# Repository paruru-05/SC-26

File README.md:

# パーツリストはPCB_Partsのそれぞれのファイルから読み取ってください。過去のものは不安定なため確定後に書き直します。

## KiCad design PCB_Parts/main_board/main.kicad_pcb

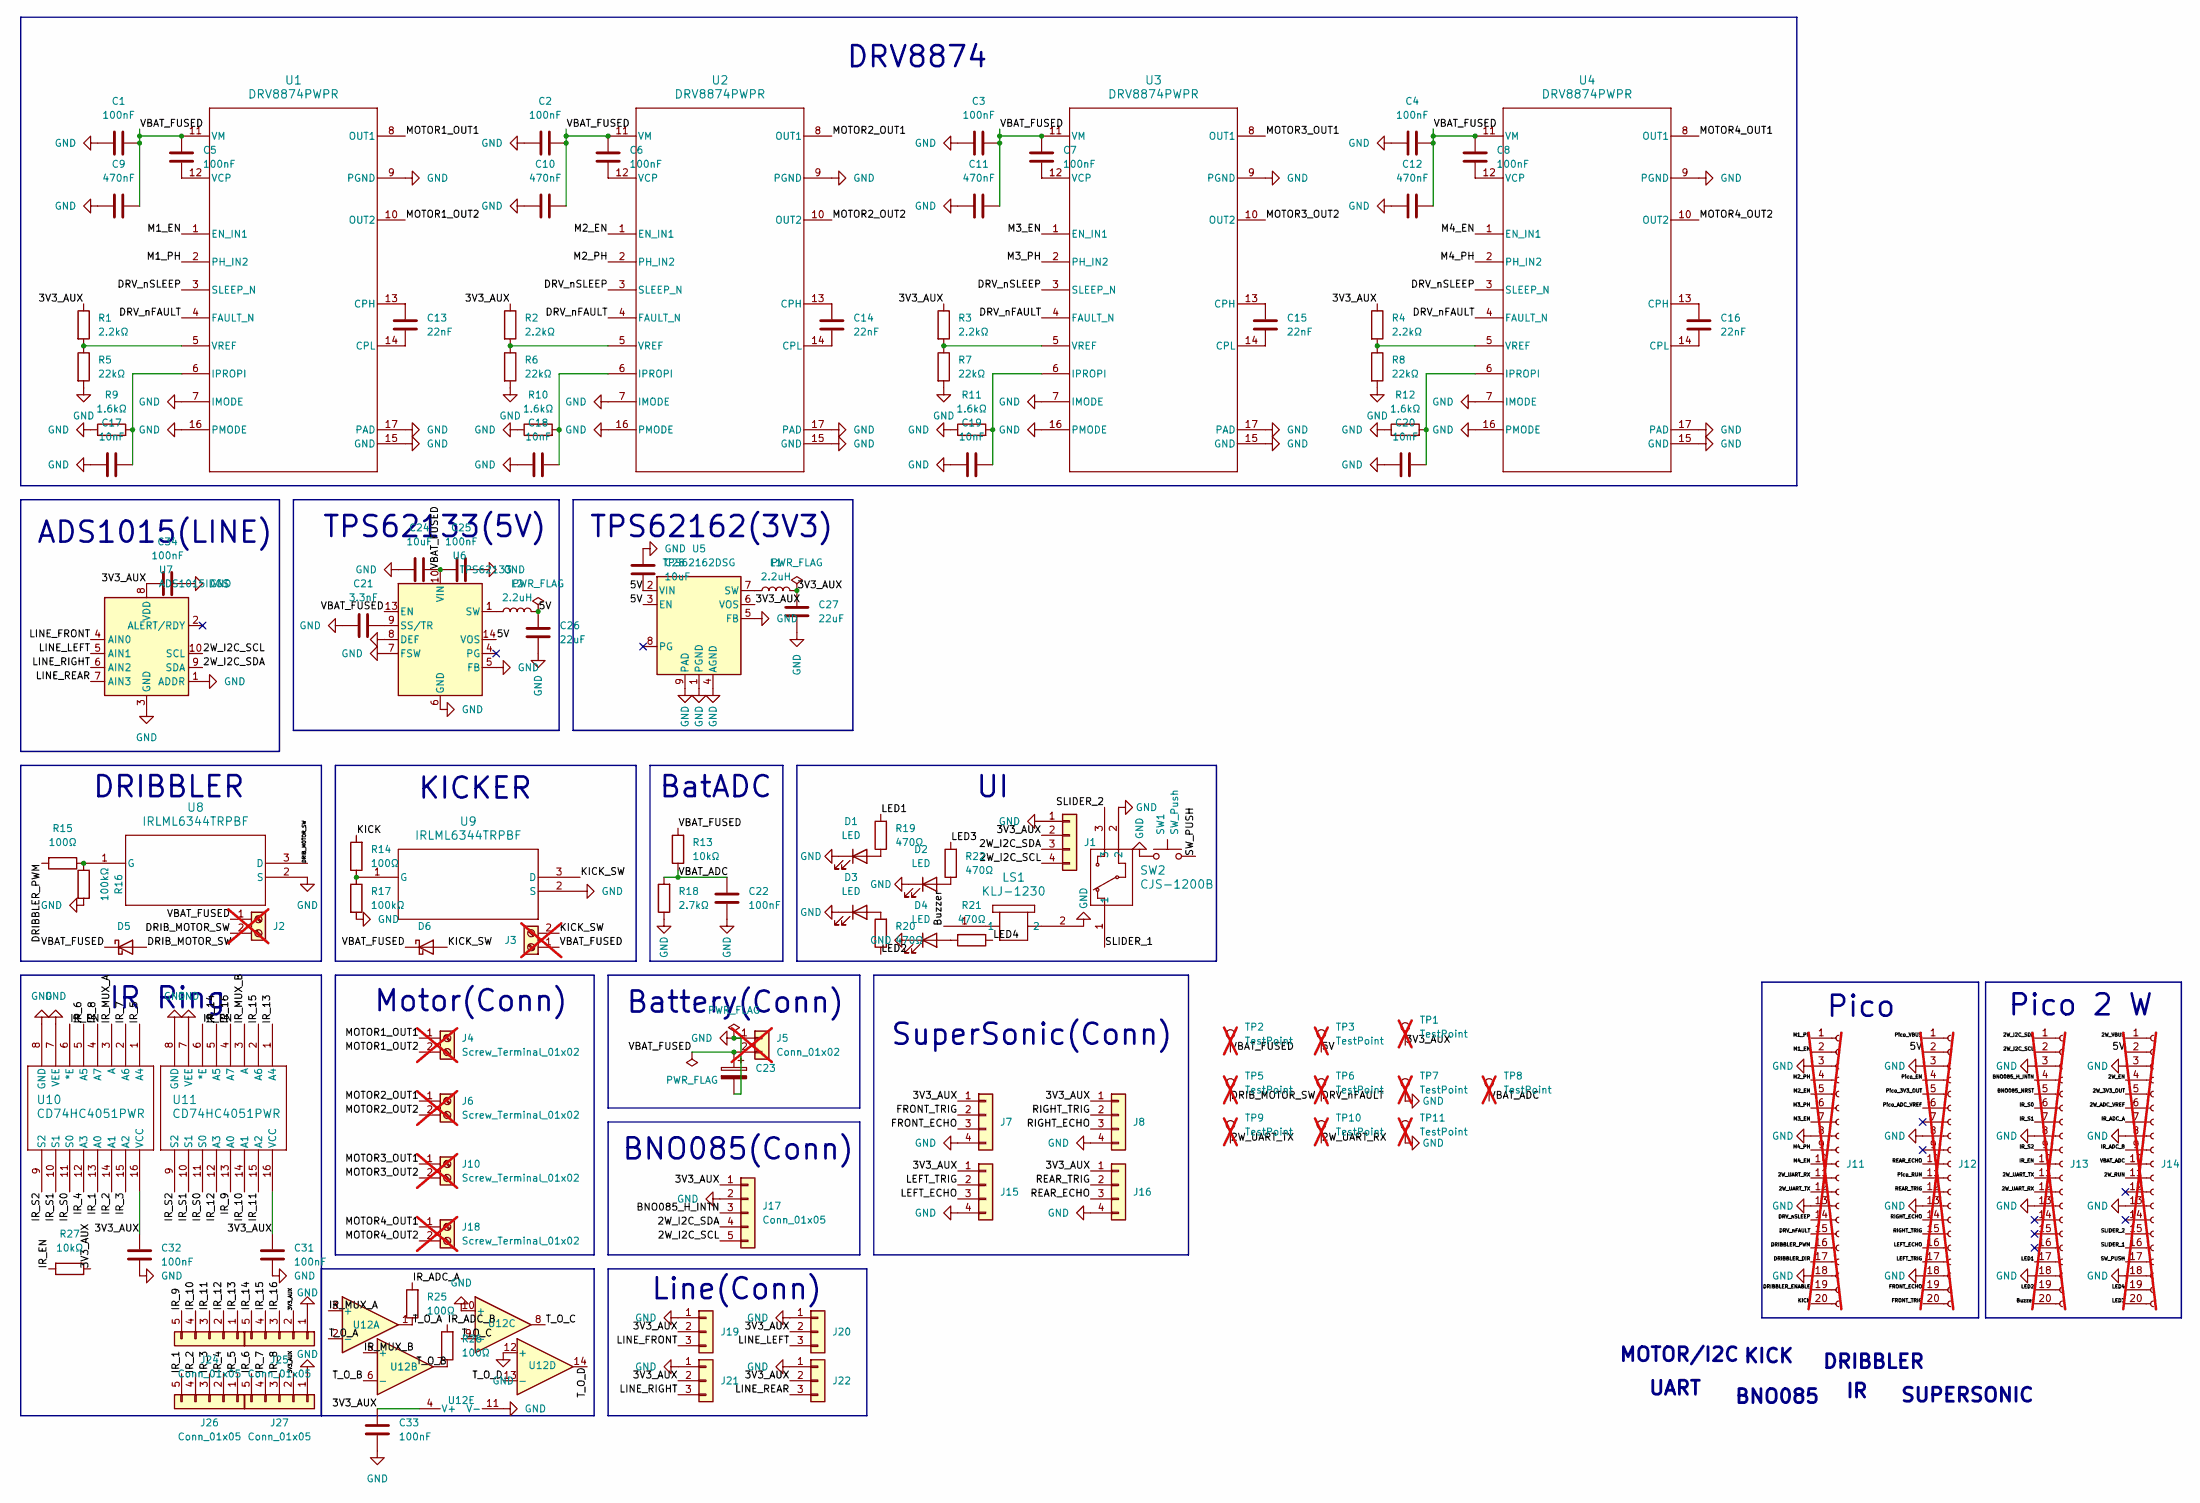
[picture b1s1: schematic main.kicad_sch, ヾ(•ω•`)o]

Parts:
C1, C2, C3, C4, C5, C6, C7, C8, C22, C25, C31, C32, C33, C34: 100nF; C_0603_1608Metric
C9, C10, C11, C12: 470nF; C_0603_1608Metric
C13, C14, C15, C16: 22nF; C_0603_1608Metric
C17, C18, C19, C20: 10nF; C_0603_1608Metric
C21: 3.3nF; C_0603_1608Metric
C23: 1000uF; CP_Elec_10x10.5
C24, C28: 10uF; C_1206_3216Metric
C26, C27: 22uF; C_1206_3216Metric
D1, D2, D3, D4: LED; LED_0603_1608Metric
D5, D6: D_Schottky; D_SMC
J1, J7, J8, J15, J16: Conn_01x04; CONN-SMD_B4B-PH-SM4-TB-LF-SN
J2, J3, J4, J6, J10, J18: Screw_Terminal_01x02; TerminalBlock_Phoenix_MKDS-1,5-2-5.08_1x02_P5.08mm_Horizont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; not fitted
J5: Conn_01x02; AMASS_XT30PW-M_1x02_P2.50mm_Horizontal; not fitted
J11, J12, J13, J14: Conn_01x20_Socket; PinSocket_1x20_P2.54mm_Vertical; not fitted
J17, J24, J25, J26, J27: Conn_01x05; CONN-SMD_5P-P2.00_B6B-PH-SM4-TB-LF-SN
J19, J20, J21, J22: Conn_01x03; CONN-SMD_B3B-PH-SM4-TB-LF-SN
L1, L2: 2.2uH; L_Coilcraft_XxL4020
LS1: KLJ-1230; KLJ-1230_KKG
R1, R2, R3, R4: 2.2kΩ; R_0603_1608Metric
R5, R6, R7, R8: 22kΩ; R_0603_1608Metric
R9, R10, R11, R12: 1.6kΩ; R_0603_1608Metric
R13, R27: 10kΩ; R_0603_1608Metric
R14, R15, R25, R26: 100Ω; R_0603_1608Metric
R16, R17: 100kΩ; R_0603_1608Metric
R18: 2.7kΩ; R_0603_1608Metric
R19, R20, R21, R22: 470Ω; R_0603_1608Metric
SW1: SW_Push; SW-SMD_L3.9-W3.0-P4.45
SW2: CJS-1200B; CJS-1200B_NDC
TP1, TP2, TP3, TP5, TP6, TP7, TP8, TP9, TP10, TP11: TestPoint; TestPoint_Pad_D3.0mm; not fitted
U1, U2, U3, U4: DRV8874PWPR; PWP0016J_N
U5: TPS62162DSG; Texas_DSG0008A_WSON-8-1EP_2x2mm_P0.5mm_EP0.9x1.6mm_ThermalV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
U6: TPS62133; VQFN-16-1EP_3x3mm_P0.5mm_EP1.68x1.68mm_ThermalVias
U7: ADS1015IDGS; TSSOP-10_3x3mm_P0.5mm
U8, U9: IRLML6344TRPBF; IRLML6344TRPBF_INF
U10, U11: CD74HC4051PWR; PW16
U12: TLV9064; TSSOP-14_4.4x5mm_P0.65mm

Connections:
/2W_3V3_OUT: J14.5
/2W_ADC_VREF: J14.6
/2W_EN: J14.4
/2W_I2C_SCL: J1.4, J13.2, J17.5, U7.10 (SCL)
/2W_I2C_SDA: J1.3, J13.1, J17.4, U7.9 (SDA)
/2W_RUN: J14.11
/2W_UART_RX: J11.11, J13.12, TP10.1 (1_1)
/2W_UART_TX: J11.12, J13.11, TP9.1 (1_1)
/2W_VBUS: J14.1
/3V3_AUX: C27.2, C31.1, C32.2, C33.1, C34.1, J1.2, J7.1, J8.1, J15.1, J16.1, J17.1, J19.2, J20.2, J21.2, J22.2, J25.2, J27.2, L1.2, R1.1, R2.1, R3.1, R4.1, R27.1, TP1.1 (1_1), U5.6 (VOS), U7.8 (VDD), U10.16 (VCC), U11.16 (VCC), U12.4 (V+)
/5V: C26.2, C28.2, J12.2, J14.2, L2.2, TP3.1 (1_1), U5.2 (VIN), U5.3 (EN), U6.14 (VOS)
/BNO085_H_INTN: J13.4, J17.3
/BNO085_NRST: J13.5
/Buzzer: J13.20, LS1.1
/DRIBBLER_DIR: J11.17
/DRIBBLER_ENABLE: J11.19
/DRIBBLER_PWM: J11.16, R15.2
/DRIB_MOTOR_SW: D5.2 (A), J2.2, TP5.1 (1_1), U8.3 (D)
/DRV_nFAULT: J11.15, TP6.1 (1_1), U1.4 (FAULT_N), U2.4 (FAULT_N), U3.4 (FAULT_N), U4.4 (FAULT_N)
/DRV_nSLEEP: J11.14, U1.3 (SLEEP_N), U2.3 (SLEEP_N), U3.3 (SLEEP_N), U4.3 (SLEEP_N)
/FRONT_ECHO: J7.3, J12.19
/FRONT_TRIG: J7.2, J12.20
/IR_1: J26.5, U10.13 (A0)
/IR_2: J26.4, U10.14 (A1)
/IR_3: J26.3, U10.15 (A2)
/IR_4: J26.2, U10.12 (A3)
/IR_5: J26.1, U10.1 (A4)
/IR_6: J27.5, U10.5 (A5)
/IR_7: J27.4, U10.2 (A6)
/IR_8: J27.3, U10.4 (A7)
/IR_9: J24.5, U11.13 (A0)
/IR_10: J24.4, U11.14 (A1)
/IR_11: J24.3, U11.15 (A2)
/IR_12: J24.2, U11.12 (A3)
/IR_13: J24.1, U11.1 (A4)
/IR_14: J25.5, U11.5 (A5)
/IR_15: J25.4, U11.2 (A6)
/IR_16: J25.3, U11.4 (A7)
/IR_ADC_A: J14.7, R25.2
/IR_ADC_B: J14.9, R26.2
/IR_EN: J13.10, R27.2, U10.6 (*E), U11.6 (*E)
/IR_MUX_A: U10.3 (A), U12.3 (+)
/IR_MUX_B: U11.3 (A), U12.5 (+)
/IR_S0: J13.6, U10.11 (S0), U11.11 (S0)
/IR_S1: J13.7, U10.10 (S1), U11.10 (S1)
/IR_S2: J13.9, U10.9 (S2), U11.9 (S2)
/KICK: J11.20, R14.2
/KICK_SW: D6.2 (A), J3.2, U9.3 (D)
/LED1: J13.17, R19.2
/LED2: J13.19, R20.1
/LED3: J14.20, R22.2
/LED4: J14.19, R21.1
/LEFT_ECHO: J12.16, J15.3
/LEFT_TRIG: J12.17, J15.2
/LINE_FRONT: J19.3, U7.4 (AIN0)
/LINE_LEFT: J20.3, U7.5 (AIN1)
/LINE_REAR: J22.3, U7.7 (AIN3)
/LINE_RIGHT: J21.3, U7.6 (AIN2)
/M1_EN: J11.2, U1.1 (EN_IN1)
/M1_PH: J11.1, U1.2 (PH_IN2)
/M2_EN: J11.5, U2.1 (EN_IN1)
/M2_PH: J11.4, U2.2 (PH_IN2)
/M3_EN: J11.7, U3.1 (EN_IN1)
/M3_PH: J11.6, U3.2 (PH_IN2)
/M4_EN: J11.10, U4.1 (EN_IN1)
/M4_PH: J11.9, U4.2 (PH_IN2)
/MOTOR1_OUT1: J4.1, U1.8 (OUT1)
/MOTOR1_OUT2: J4.2, U1.10 (OUT2)
/MOTOR2_OUT1: J6.1, U2.8 (OUT1)
/MOTOR2_OUT2: J6.2, U2.10 (OUT2)
/MOTOR3_OUT1: J10.1, U3.8 (OUT1)
/MOTOR3_OUT2: J10.2, U3.10 (OUT2)
/MOTOR4_OUT1: J18.1, U4.8 (OUT1)
/MOTOR4_OUT2: J18.2, U4.10 (OUT2)
/Pico_3V3_OUT: J12.5
/Pico_ADC_VREF: J12.6
/Pico_EN: J12.4
/Pico_RUN: J12.11
/Pico_VBUS: J12.1
/REAR_ECHO: J12.10, J16.3
/REAR_TRIG: J12.12, J16.2
/RIGHT_ECHO: J8.3, J12.14
/RIGHT_TRIG: J8.2, J12.15
/SLIDER_1: J14.16, SW2.1
/SLIDER_2: J14.15, SW2.3
/SW_PUSH: J14.17, SW1.2
/T_O_A: R25.1, U12.1, U12.2 (-)
/T_O_B: R26.1, U12.6 (-), U12.7
/T_O_C: U12.8, U12.9 (-)
/T_O_D: U12.13 (-), U12.14
/VBAT_ADC: C22.2, J14.10, R13.1, R18.2, TP8.1 (1_1)
/VBAT_FUSED: C1.2, C2.2, C3.2, C4.2, C5.1, C6.1, C7.1, C8.1, C9.2, C10.2, C11.2, C12.2, C23.1, C24.2, C25.2, D5.1 (K), D6.1 (K), J2.1, J3.1, J5.2, R13.2, TP2.1 (1_1), U1.11 (VM), U2.11 (VM), U3.11 (VM), U4.11 (VM), U6.10 (VIN), U6.11 (VIN), U6.12 (VIN), U6.13 (EN)
GND: C1.1, C2.1, C3.1, C4.1, C9.1, C10.1, C11.1, C12.1, C17.1, C18.1, C19.2, C20.1, C21.1, C22.1, C23.2, C24.1, C25.1, C26.1, C27.1, C28.1, C31.2, C32.1, C33.2, C34.2, D1.1 (K), D2.1 (K), D3.1 (K), D4.1 (K), J1.1, J5.1, J7.4, J8.4, J11.3, J11.8, J11.13, J11.18, J12.3, J12.8, J12.13, J12.18, J13.3, J13.8, J13.13, J13.18, J14.3, J14.8, J14.13, J14.18, J15.4, J16.4, J17.2, J19.1, J20.1, J21.1, J22.1, J25.1, J27.1, LS1.2, R5.2, R6.2, R7.2, R8.2, R9.1, R10.1, R11.1, R12.1, R16.2, R17.2, R18.1, SW1.1, SW2.2, TP7.1 (1_1), TP11.1 (1_1), U1.7 (IMODE), U1.9 (PGND), U1.15 (GND), U1.16 (PMODE), U1.17 (PAD), U2.7 (IMODE), U2.9 (PGND), U2.15 (GND), U2.16 (PMODE), U2.17 (PAD), U3.7 (IMODE), U3.9 (PGND), U3.15 (GND), U3.16 (PMODE), U3.17 (PAD), U4.7 (IMODE), U4.9 (PGND), U4.15 (GND), U4.16 (PMODE), U4.17 (PAD), U5.1 (PGND), U5.4 (AGND), U5.5 (FB), U5.9 (PAD), U6.5 (FB), U6.6 (GND), U6.7 (FSW), U6.8 (DEF), U6.15 (GND), U6.16 (GND), U6.17 (GND), U7.1 (ADDR), U7.3 (GND), U8.2 (S), U9.2 (S), U10.7 (VEE), U10.8 (GND), U11.7 (VEE), U11.8 (GND), U12.10 (+), U12.11 (V-), U12.12 (+)
unnamed: D1.2 (A), R19.1
unnamed: D2.2 (A), R22.1
unnamed: D3.2 (A), R20.2
unnamed: D4.2 (A), R21.2
unnamed: L2.1, U6.1 (SW), U6.2 (SW), U6.3 (SW)
unnamed: C13.1, U1.13 (CPH)
unnamed: C13.2, U1.14 (CPL)
unnamed: C17.2, R9.2, U1.6 (IPROPI)
unnamed: C5.2, U1.12 (VCP)
unnamed: R1.2, R5.1, U1.5 (VREF)
unnamed: C14.1, U2.13 (CPH)
unnamed: C14.2, U2.14 (CPL)
unnamed: C18.2, R10.2, U2.6 (IPROPI)
unnamed: C6.2, U2.12 (VCP)
unnamed: R2.2, R6.1, U2.5 (VREF)
unnamed: C15.1, U3.13 (CPH)
unnamed: C15.2, U3.14 (CPL)
unnamed: C19.1, R11.2, U3.6 (IPROPI)
unnamed: C7.2, U3.12 (VCP)
unnamed: R3.2, R7.1, U3.5 (VREF)
unnamed: C16.1, U4.13 (CPH)
unnamed: C16.2, U4.14 (CPL)
unnamed: C20.2, R12.2, U4.6 (IPROPI)
unnamed: C8.2, U4.12 (VCP)
unnamed: R4.2, R8.1, U4.5 (VREF)
unnamed: L1.1, U5.7 (SW)
unnamed: C21.2, U6.9 (SS/TR)
unnamed: R15.1, R16.1, U8.1 (G)
unnamed: R14.1, R17.1, U9.1 (G)

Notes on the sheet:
KICKER
BNO085(Conn)
DRIBBLER
SUPERSONIC
TPS62162(3V3)
SuperSonic(Conn)
BNO085
BatADC
DRV8874
TPS62133(5V)
KICK
Line(Conn)
UART
Pico
Pico 2 W
Battery(Conn)
IR Ring
MOTOR/I2C
ADS1015(LINE)
Motor(Conn)

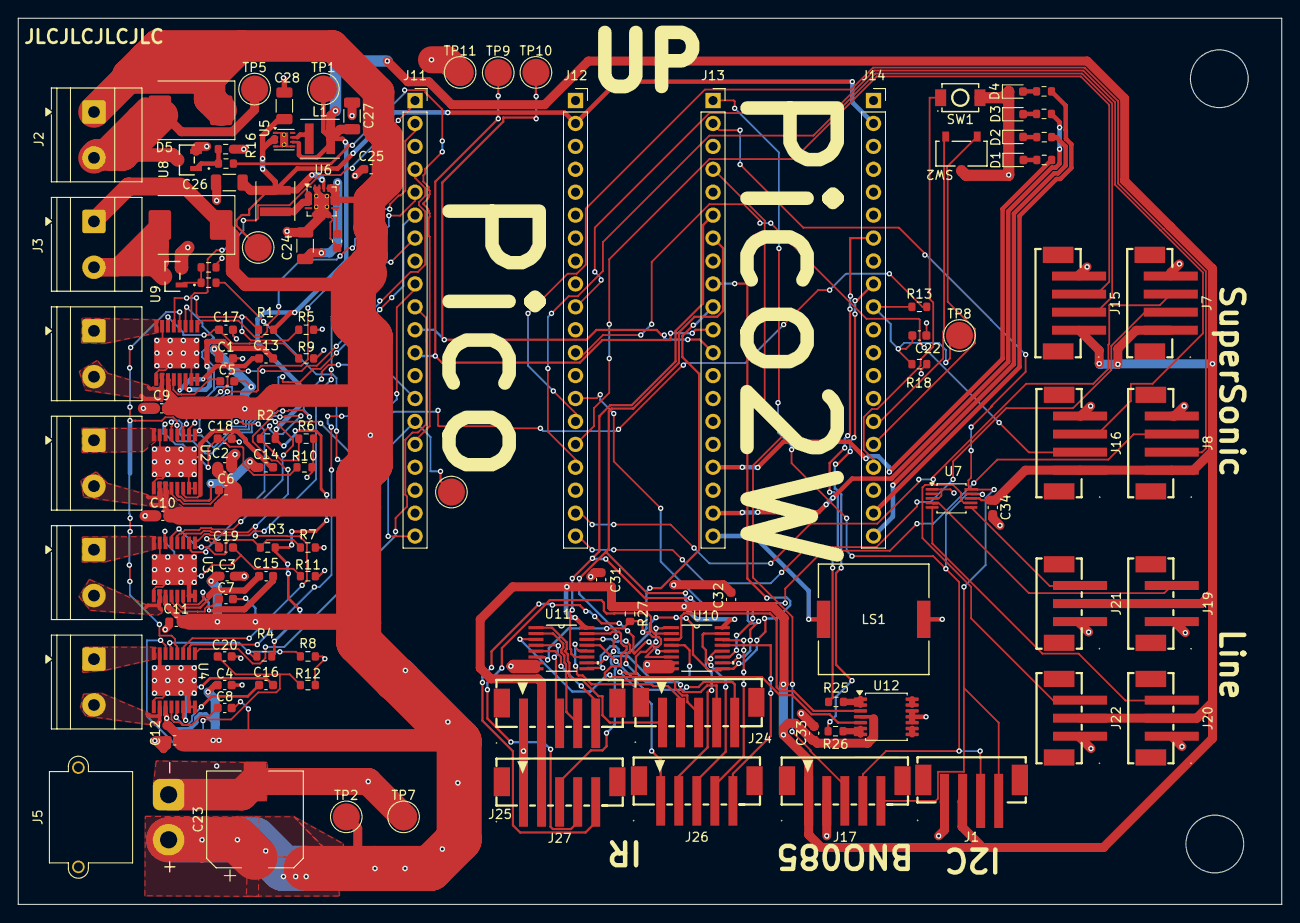
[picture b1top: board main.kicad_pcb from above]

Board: 2 copper layers, 140.0 x 98.2 mm, 115 parts (0 on the bottom side), 109 nets.

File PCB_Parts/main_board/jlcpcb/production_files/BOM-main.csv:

Comment,Designator,Footprint,LCSC,Quantity
1.6kΩ,"R10,R11,R12,R9",R_0603_1608Metric,C22369888,4
1000uF,C23,CP_Elec_10x10.5,C7471896,1
100kΩ,"R16,R17",R_0603_1608Metric,C25803,2
100nF,"C1,C2,C22,C25,C3,C31,C32,C33,C34,C4,C5,C6,C7,C8",C_0603_1608Metric,C14663,14
100Ω,"R14,R15,R25,R26",R_0603_1608Metric,C22775,4
10kΩ,"R13,R27",R_0603_1608Metric,C25804,2
10nF,"C17,C18,C19,C20",C_0603_1608Metric,C57112,4
10uF,"C24,C28",C_1206_3216Metric,C13585,2
2.2kΩ,"R1,R2,R3,R4",R_0603_1608Metric,C4190,4
2.2uH,"L1,L2",L_Coilcraft_XxL4020,C122469,2
2.7kΩ,R18,R_0603_1608Metric,C13167,1
22kΩ,"R5,R6,R7,R8",R_0603_1608Metric,C31850,4
22nF,"C13,C14,C15,C16",C_0603_1608Metric,C21122,4
22uF,"C26,C27",C_1206_3216Metric,C12891,2
3.3nF,C21,C_0603_1608Metric,C1613,1
470nF,"C10,C11,C12,C9",C_0603_1608Metric,C1623,4
470Ω,"R19,R20,R21,R22",R_0603_1608Metric,C23179,4
ADS1015IDGS,U7,TSSOP-10_3x3mm_P0.5mm,C193969,1
CD74HC4051PWR,"U10,U11",PW16,C352826,2
CJS-1200B,SW2,CJS-1200B_NDC,C3664500,1
Conn_01x03,"J19,J20,J21,J22",CONN-SMD_B3B-PH-SM4-TB-LF-SN,C160353,4
Conn_01x04,"J1,J15,J16,J7,J8",CONN-SMD_B4B-PH-SM4-TB-LF-SN,C160354,5
Conn_01x05,"J17,J24,J25,J26,J27",CONN-SMD_5P-P2.00_B6B-PH-SM4-TB-LF-SN,C265085,5
DRV8874PWPR,"U1,U2,U3,U4",PWP0016J_N,C1855818,4
D_Schottky,"D5,D6",D_SMC,C174037,2
IRLML6344TRPBF,"U8,U9",IRLML6344TRPBF_INF,C6285738,2
KLJ-1230,LS1,KLJ-1230_KKG,C201042,1
LED,D1,LED_0603_1608Metric,C2286,1
LED,D3,LED_0603_1608Metric,C2287,1
LED,D2,LED_0603_1608Metric,C2288,1
LED,D4,LED_0603_1608Metric,C52675996,1
SW_Push,SW1,SW-SMD_L3.9-W3.0-P4.45,C720477,1
TLV9064,U12,TSSOP-14_4.4x5mm_P0.65mm,C779410,1
TPS62133,U6,VQFN-16-1EP_3x3mm_P0.5mm_EP1.68x1.68mm_ThermalVias,C73973,1
TPS62162DSG,U5,Texas_DSG0008A_WSON-8-1EP_2x2mm_P0.5mm_EP0.9x1.6mm_ThermalVias,C40256,1

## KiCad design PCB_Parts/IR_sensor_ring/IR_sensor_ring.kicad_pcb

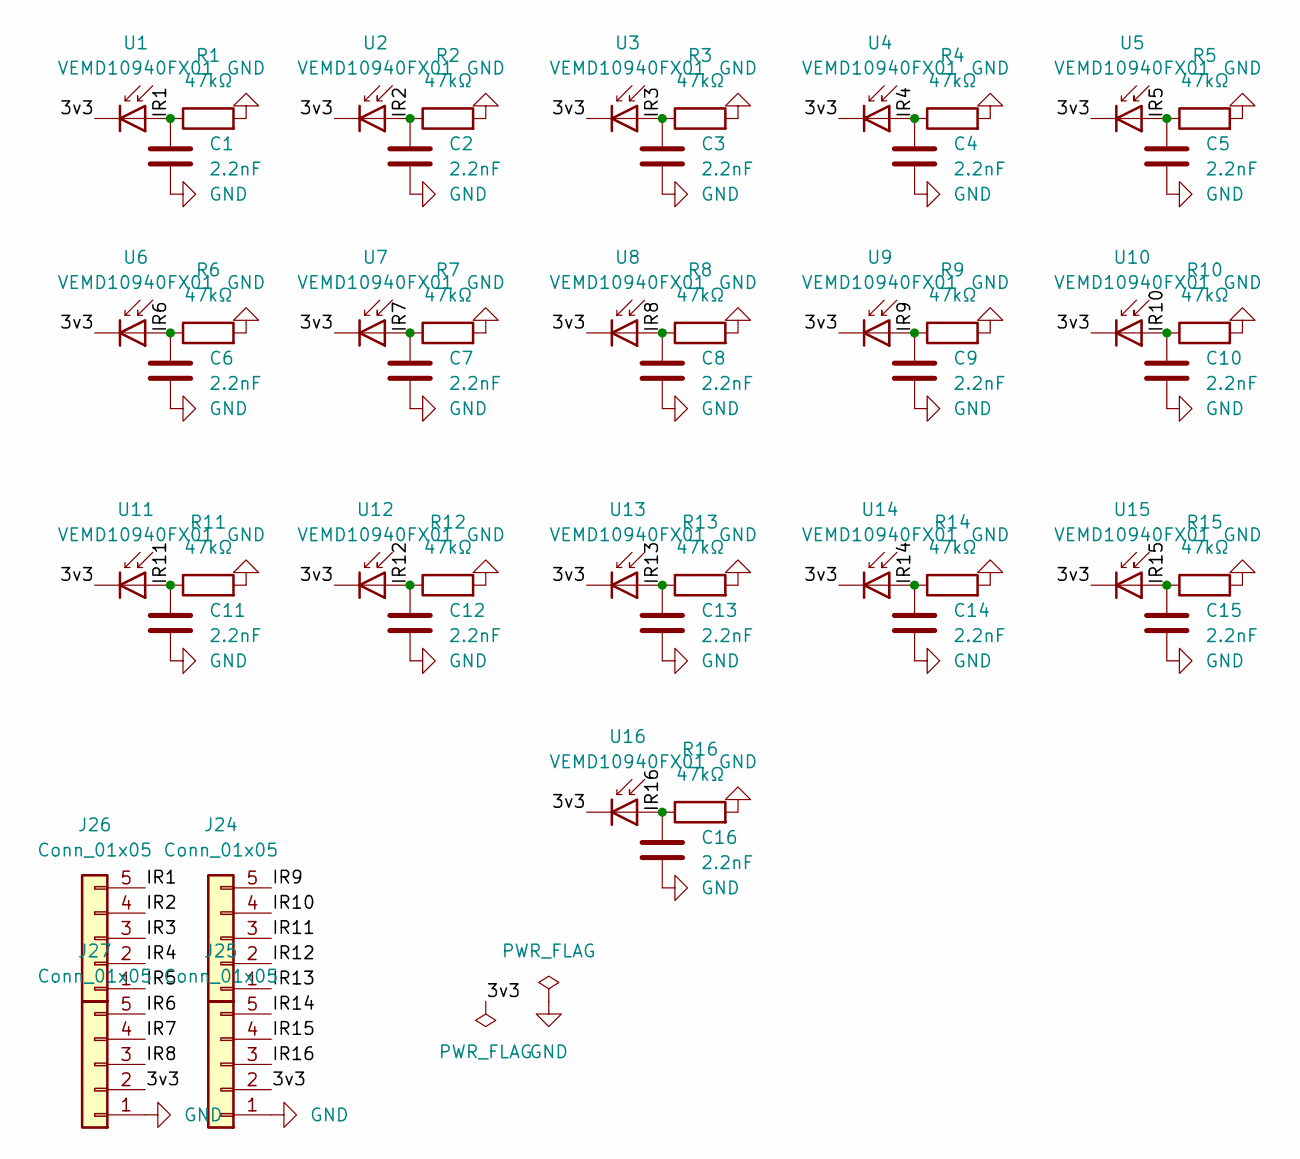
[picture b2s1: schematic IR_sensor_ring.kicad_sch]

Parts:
C1, C2, C3, C4, C5, C6, C7, C8, C9, C10, C11, C12, C13, C14, C15, C16: 2.2nF; C_0603_1608Metric; LCSC Part C1604
J24, J25, J26, J27: Conn_01x05; CONN-SMD_5P-P2.00_B6B-PH-SM4-TB-LF-SN
R1, R2, R3, R4, R5, R6, R7, R8, R9, R10, R11, R12, R13, R14, R15, R16: 47kΩ; R_0603_1608Metric; LCSC Part C25819
U1, U2, U3, U4, U5, U6, U7, U8, U9, U10, U11, U12, U13, U14, U15, U16: VEMD10940FX01; LED-SMD_3P-L3.0-W2.0_LTE-S3201L-ZB-HT; MPN VEMD10940FX01; LCSC Part C7104273

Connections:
/3v3: J25.2, J27.2, U1.1 (K), U2.1 (K), U3.1 (K), U4.1 (K), U5.1 (K), U6.1 (K), U7.1 (K), U8.1 (K), U9.1 (K), U10.1 (K), U11.1 (K), U12.1 (K), U13.1 (K), U14.1 (K), U15.1 (K), U16.1 (K)
/IR1: C1.2, J26.5, R1.1, U1.2 (A)
/IR2: C2.2, J26.4, R2.1, U2.2 (A)
/IR3: C3.2, J26.3, R3.1, U3.2 (A)
/IR4: C4.2, J26.2, R4.1, U4.2 (A)
/IR5: C5.2, J26.1, R5.1, U5.2 (A)
/IR6: C6.2, J27.5, R6.1, U6.2 (A)
/IR7: C7.2, J27.4, R7.1, U7.2 (A)
/IR8: C8.2, J27.3, R8.1, U8.2 (A)
/IR9: C9.2, J24.5, R9.1, U9.2 (A)
/IR10: C10.2, J24.4, R10.1, U10.2 (A)
/IR11: C11.2, J24.3, R11.1, U11.2 (A)
/IR12: C12.2, J24.2, R12.1, U12.2 (A)
/IR13: C13.2, J24.1, R13.1, U13.2 (A)
/IR14: C14.2, J25.5, R14.1, U14.2 (A)
/IR15: C15.2, J25.4, R15.1, U15.2 (A)
/IR16: C16.2, J25.3, R16.1, U16.2 (A)
GND: C1.1, C2.1, C3.1, C4.1, C5.1, C6.1, C7.1, C8.1, C9.1, C10.1, C11.1, C12.1, C13.1, C14.1, C15.1, C16.1, J25.1, J27.1, R1.2, R2.2, R3.2, R4.2, R5.2, R6.2, R7.2, R8.2, R9.2, R10.2, R11.2, R12.2, R13.2, R14.2, R15.2, R16.2

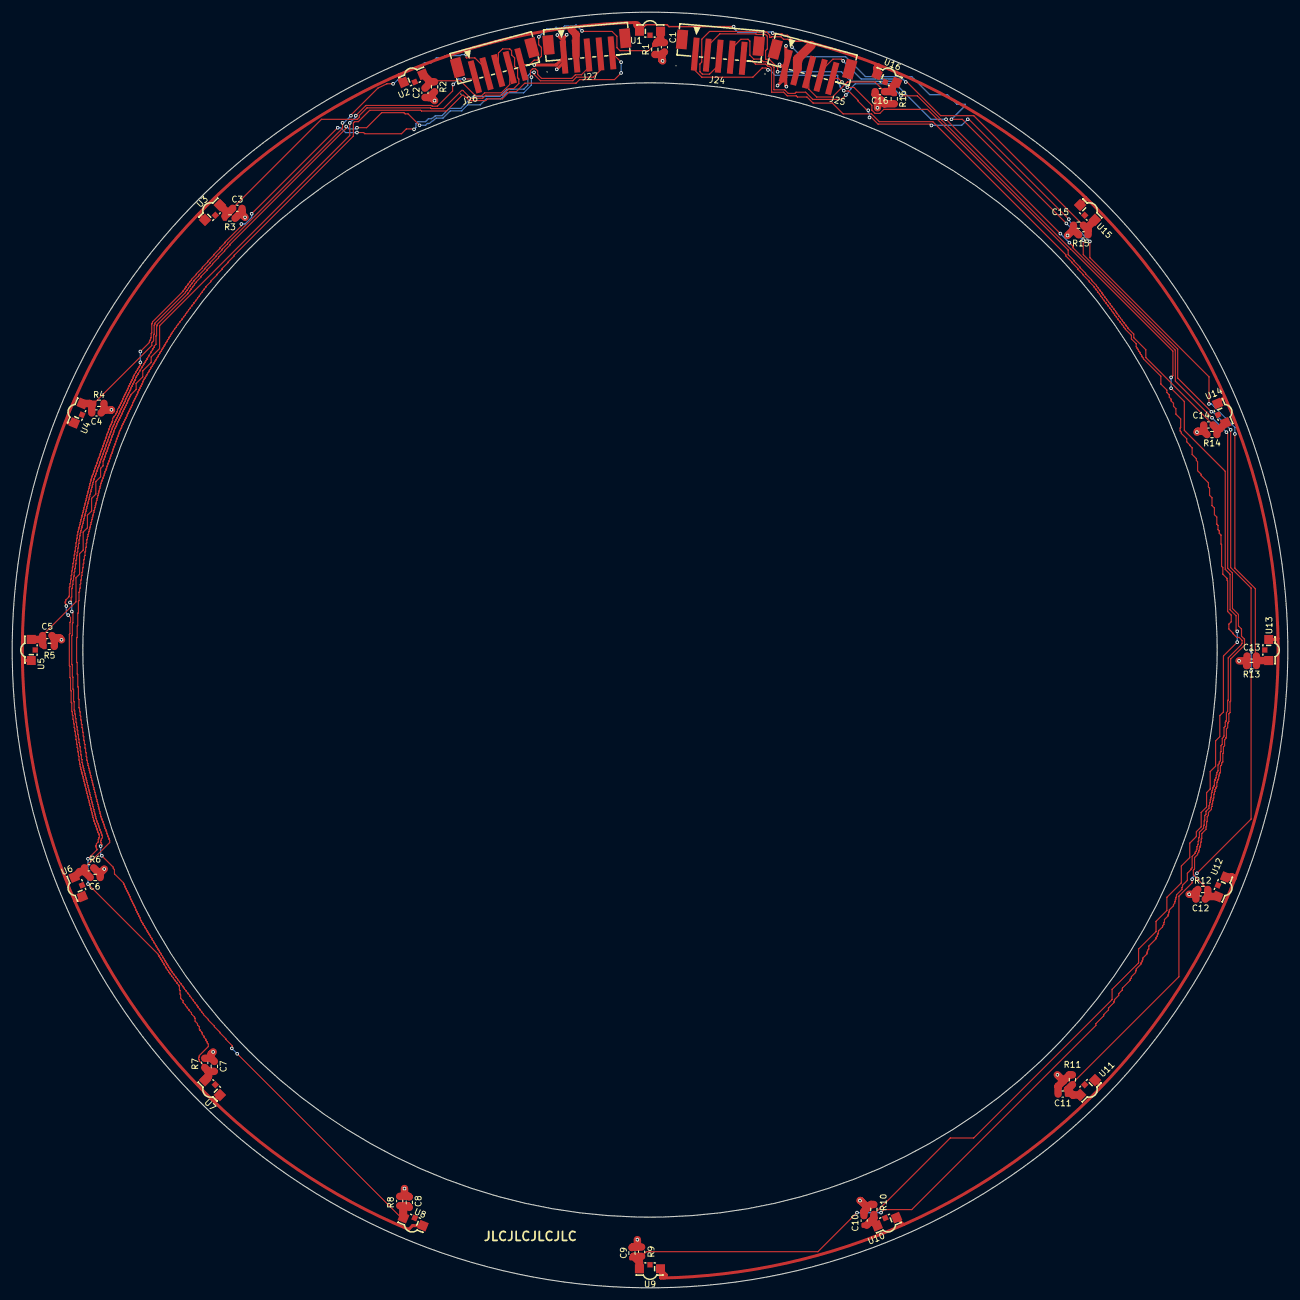
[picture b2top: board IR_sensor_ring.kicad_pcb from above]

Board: 2 copper layers, 212.0 x 212.0 mm, 52 parts (0 on the bottom side), 18 nets.

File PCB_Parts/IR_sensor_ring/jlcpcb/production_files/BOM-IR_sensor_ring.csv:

Comment,Designator,Footprint,LCSC,Quantity
2.2nF,"C1,C10,C11,C12,C13,C14,C15,C16,C2,C3,C4,C5,C6,C7,C8,C9",C_0603_1608Metric,C1604,16
47kΩ,"R1,R10,R11,R12,R13,R14,R15,R16,R2,R3,R4,R5,R6,R7,R8,R9",R_0603_1608Metric,C25819,16
Conn_01x05,"J24,J25,J26,J27",CONN-SMD_5P-P2.00_B6B-PH-SM4-TB-LF-SN,C265085,4
VEMD10940FX01,"U1,U10,U11,U12,U13,U14,U15,U16,U2,U3,U4,U5,U6,U7,U8,U9",LED-SMD_3P-L3.0-W2.0_LTE-S3201L-ZB-HT,C7104273,16

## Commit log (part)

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2026-04-19 慣性です
2026-04-19 もう一回完成h
2026-04-20 Update README with revised budget and item list
    Removed the connector cable entry and updated totals.
2026-04-20 Update pricing and product details in README
2026-04-20 Update README with new sensor and budget details
2026-04-21 Revise item list and total budget in README
    Updated the budget and item list in the README, including new items and their prices.
2026-04-22 Add table of contents to README.md
2026-04-22 Revise README formatting and content
    Updated the README to improve formatting and clarity, including a new table of contents and additional details for product descriptions.
2026-04-22 Add links to parts categories in README
2026-05-08 changeee
2026-05-09 add ignore
2026-05-09 Update .gitignore and remove ignored files from index
2026-05-09 modify ignore
2026-05-10 0:50
2026-05-10 aaaa
2026-06-10 アップデート
